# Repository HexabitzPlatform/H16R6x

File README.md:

# H16R6x-Hardware
Hexabitz 8*8 RGB LED Matrix Display Module Hardware Design

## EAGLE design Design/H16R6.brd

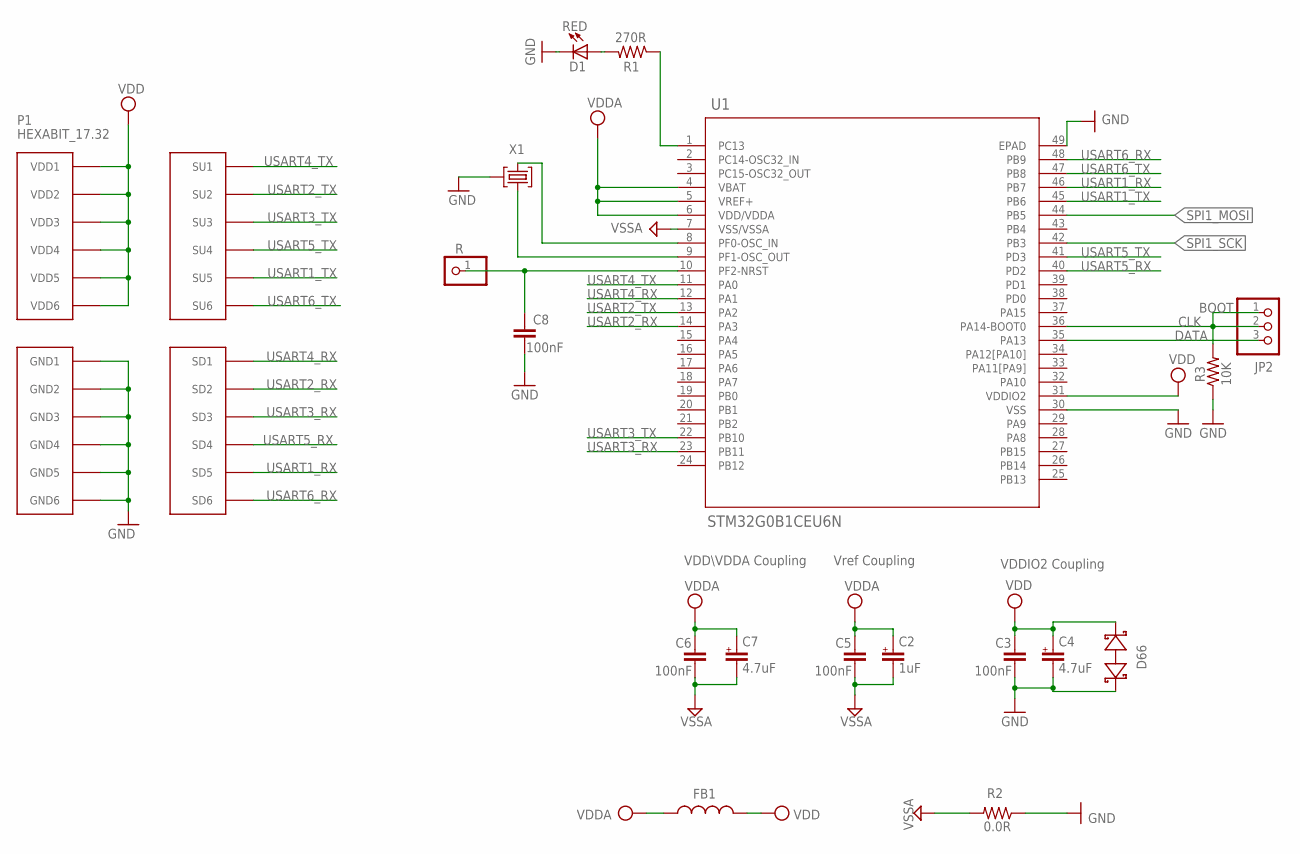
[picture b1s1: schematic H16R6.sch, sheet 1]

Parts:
C2: 1uF; C-0402-POL
C3, C5, C6, C8: 100nF; C-0402
C4, C7: 4.7uF; C-0402-POL
D1: RED; VLMS1300-GS08; MPN VLMS1300-GS08
D66: BOURNS_CDSOD323-T03SCBOURNS_CDSOD323-T03SC_0_0; BOURNS_CDSOD323-T03SC_0
FB1: FB-TDK_MMZ1608Y300B; MPN MMZ1608Y300B
JP2: PINHD-1X3; 1X03
P1: HEXABIT_17.32
R: R; 1X01
R1: 270R; R-0402
R2: 0.0R; R-0402; MPN RC0603JR-070RL
R3: 10K; R-0402
TRIMBLE-LOGO1: HEXA-LOGO
U1: STM32G0B1CEU6N; HEXABITZ_ICS_QFN_B1CEU6_STM-L
X1: XTALL_CSTCE8M00G52

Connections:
CLK: JP2.1, JP2.2, R3.2, U1.36 (PA14-BOOT0)
DATA: JP2.3, U1.35 (PA13)
GND: C3.2, C4.2, C8.2, D1.C, D66.1 (A), P1.PAD_PD7 (GND1), P1.PAD_PD8 (GND2), P1.PAD_PD9 (GND3), P1.PAD_PD10 (GND4), P1.PAD_PD11 (GND5), P1.PAD_PD12 (GND6), R2.1, R3.1, U1.30 (VSS), U1.49 (EPAD), X1.P$2 (2); also elsewhere on the board
unnamed: D1.A, R1.2
unnamed: C8.1, R.1, U1.10 (PF2-NRST)
unnamed: U1.9 (PF1-OSC_OUT), X1.P$1 (1)
unnamed: U1.8 (PF0-OSC_IN), X1.P$3 (3)
unnamed: R1.1, U1.1 (PC13)
SPI1_MOSI: U1.44 (PB5); also elsewhere on the board
SPI1_SCK: U1.42 (PB3); also elsewhere on the board
USART1_RX: P1.PAD_PD5 (SD5), U1.46 (PB7)
USART1_TX: P1.PAD_PU5 (SU5), U1.45 (PB6)
USART2_RX: P1.PAD_PD2 (SD2), U1.14 (PA3)
USART2_TX: P1.PAD_PU2 (SU2), U1.13 (PA2)
USART3_RX: P1.PAD_PD3 (SD3), U1.23 (PB11)
USART3_TX: P1.PAD_PU3 (SU3), U1.22 (PB10)
USART4_RX: P1.PAD_PD1 (SD1), U1.12 (PA1)
USART4_TX: P1.PAD_PU1 (SU1), U1.11 (PA0)
USART5_RX: P1.PAD_PD4 (SD4), U1.40 (PD2)
USART5_TX: P1.PAD_PU4 (SU4), U1.41 (PD3)
USART6_RX: P1.PAD_PD6 (SD6), U1.48 (PB9)
USART6_TX: P1.PAD_PU6 (SU6), U1.47 (PB8)
VDD: C3.1, C4.1, D66.2 (C), FB1.2, P1.PAD_PU7 (VDD1), P1.PAD_PU8 (VDD2), P1.PAD_PU9 (VDD3), P1.PAD_PU10 (VDD4), P1.PAD_PU11 (VDD5), P1.PAD_PU12 (VDD6), U1.31 (VDDIO2); also elsewhere on the board
VDDA: C2.1, C5.1, C6.1, C7.1, FB1.1, U1.4 (VBAT), U1.5 (VREF+), U1.6 (VDD/VDDA)
VSSA: C2.2, C5.2, C6.2, C7.2, R2.2, U1.7 (VSS/VSSA)

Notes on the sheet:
Vref Coupling
VDDIO2 Coupling
VDD\VDDA Coupling
BOOT

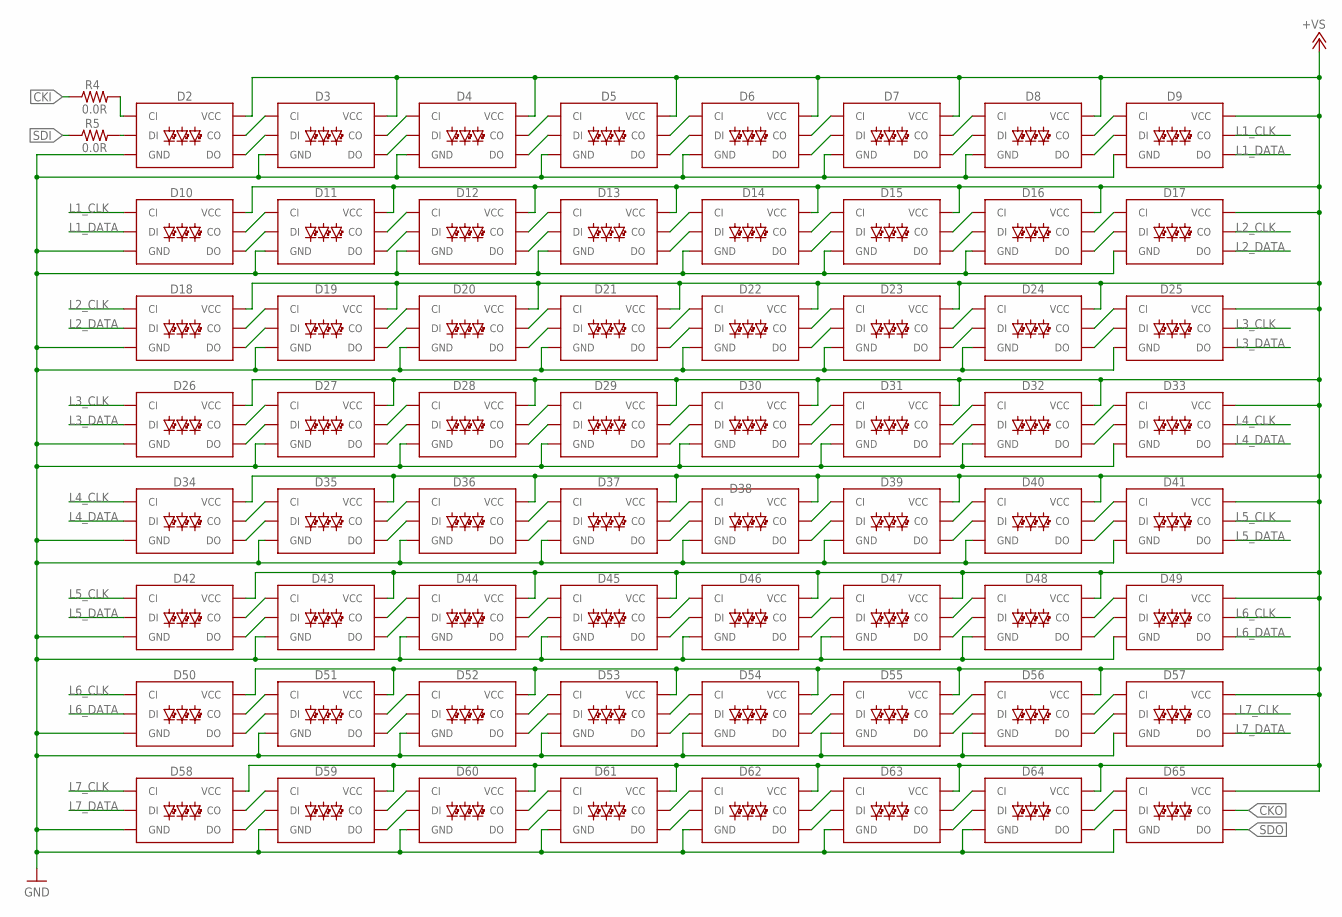
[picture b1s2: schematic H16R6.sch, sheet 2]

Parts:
D2, D3, D4, D5, D6, D7, D8, D9, D10, D11, D12, D13, D14, D15, D16, D17, D18, D19, D20, D21, D22, D23, D24, D25, D26, D27, D28, D29, D30, D31, D32, D33, D34, D35, D36, D37, D38, D39, D40, D41, D42, D43, D44, D45, D46, D47, D48, D49, D50, D51, D52, D53, D54, D55, D56, D57, D58, D59, D60, D61, D62, D63, D64, D65: SPARKFUN-LED_APA102-2020
R4, R5: 0.0R; R-0402

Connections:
+VS: D2.VDD (VCC), D2.VDD1 (VCC), D3.VDD (VCC), D3.VDD1 (VCC), D4.VDD (VCC), D4.VDD1 (VCC), D5.VDD (VCC), D5.VDD1 (VCC), D6.VDD (VCC), D6.VDD1 (VCC), D7.VDD (VCC), D7.VDD1 (VCC), D8.VDD (VCC), D8.VDD1 (VCC), D9.VDD (VCC), D9.VDD1 (VCC), D10.VDD (VCC), D10.VDD1 (VCC), D11.VDD (VCC), D11.VDD1 (VCC), D12.VDD (VCC), D12.VDD1 (VCC), D13.VDD (VCC), D13.VDD1 (VCC), D14.VDD (VCC), D14.VDD1 (VCC), D15.VDD (VCC), D15.VDD1 (VCC), D16.VDD (VCC), D16.VDD1 (VCC), D17.VDD (VCC), D17.VDD1 (VCC), D18.VDD (VCC), D18.VDD1 (VCC), D19.VDD (VCC), D19.VDD1 (VCC), D20.VDD (VCC), D20.VDD1 (VCC), D21.VDD (VCC), D21.VDD1 (VCC), D22.VDD (VCC), D22.VDD1 (VCC), D23.VDD (VCC), D23.VDD1 (VCC), D24.VDD (VCC), D24.VDD1 (VCC), D25.VDD (VCC), D25.VDD1 (VCC), D26.VDD (VCC), D26.VDD1 (VCC), D27.VDD (VCC), D27.VDD1 (VCC), D28.VDD (VCC), D28.VDD1 (VCC), D29.VDD (VCC), D29.VDD1 (VCC), D30.VDD (VCC), D30.VDD1 (VCC), D31.VDD (VCC), D31.VDD1 (VCC), D32.VDD (VCC), D32.VDD1 (VCC), D33.VDD (VCC), D33.VDD1 (VCC), D34.VDD (VCC), D34.VDD1 (VCC), D35.VDD (VCC), D35.VDD1 (VCC), D36.VDD (VCC), D36.VDD1 (VCC), D37.VDD (VCC), D37.VDD1 (VCC), D38.VDD (VCC), D38.VDD1 (VCC), D39.VDD (VCC), D39.VDD1 (VCC), D40.VDD (VCC), D40.VDD1 (VCC), D41.VDD (VCC), D41.VDD1 (VCC), D42.VDD (VCC), D42.VDD1 (VCC), D43.VDD (VCC), D43.VDD1 (VCC), D44.VDD (VCC), D44.VDD1 (VCC), D45.VDD (VCC), D45.VDD1 (VCC), D46.VDD (VCC), D46.VDD1 (VCC), D47.VDD (VCC), D47.VDD1 (VCC), D48.VDD (VCC), D48.VDD1 (VCC), D49.VDD (VCC), D49.VDD1 (VCC), D50.VDD (VCC), D50.VDD1 (VCC), D51.VDD (VCC), D51.VDD1 (VCC), D52.VDD (VCC), D52.VDD1 (VCC), D53.VDD (VCC), D53.VDD1 (VCC), D54.VDD (VCC), D54.VDD1 (VCC), D55.VDD (VCC), D55.VDD1 (VCC), D56.VDD (VCC), D56.VDD1 (VCC), D57.VDD (VCC), D57.VDD1 (VCC), D58.VDD (VCC), D58.VDD1 (VCC), D59.VDD (VCC), D59.VDD1 (VCC), D60.VDD (VCC), D60.VDD1 (VCC), D61.VDD (VCC), D61.VDD1 (VCC), D62.VDD (VCC), D62.VDD1 (VCC), D63.VDD (VCC), D63.VDD1 (VCC), D64.VDD (VCC), D64.VDD1 (VCC), D65.VDD (VCC), D65.VDD1 (VCC); also elsewhere on the board
CKI: R4.1; also elsewhere on the board
CKO: D65.CO; also elsewhere on the board
GND: D2.GND, D3.GND, D4.GND, D5.GND, D6.GND, D7.GND, D8.GND, D9.GND, D10.GND, D11.GND, D12.GND, D13.GND, D14.GND, D15.GND, D16.GND, D17.GND, D18.GND, D19.GND, D20.GND, D21.GND, D22.GND, D23.GND, D24.GND, D25.GND, D26.GND, D27.GND, D28.GND, D29.GND, D30.GND, D31.GND, D32.GND, D33.GND, D34.GND, D35.GND, D36.GND, D37.GND, D38.GND, D39.GND, D40.GND, D41.GND, D42.GND, D43.GND, D44.GND, D45.GND, D46.GND, D47.GND, D48.GND, D49.GND, D50.GND, D51.GND, D52.GND, D53.GND, D54.GND, D55.GND, D56.GND, D57.GND, D58.GND, D59.GND, D60.GND, D61.GND, D62.GND, D63.GND, D64.GND, D65.GND; also elsewhere on the board
L1_CLK: D9.CO, D10.CI
L1_DATA: D9.DO, D10.DI
L2_CLK: D17.CO, D18.CI
L2_DATA: D17.DO, D18.DI
L3_CLK: D25.CO, D26.CI
L3_DATA: D25.DO, D26.DI
L4_CLK: D33.CO, D34.CI
L4_DATA: D33.DO, D34.DI
L5_CLK: D41.CO, D42.CI
L5_DATA: D41.DO, D42.DI
L6_CLK: D49.CO, D50.CI
L6_DATA: D49.DO, D50.DI
L7_CLK: D57.CO, D58.CI
L7_DATA: D57.DO, D58.DI
unnamed: D3.DO, D4.DI
unnamed: D3.CO, D4.CI
unnamed: D2.DO, D3.DI
unnamed: D2.CO, D3.CI
unnamed: D8.DO, D9.DI
unnamed: D8.CO, D9.CI
unnamed: D7.CO, D8.CI
unnamed: D7.DO, D8.DI
unnamed: D5.CO, D6.CI
unnamed: D5.DO, D6.DI
unnamed: D16.CO, D17.CI
unnamed: D16.DO, D17.DI
unnamed: D10.CO, D11.CI
unnamed: D10.DO, D11.DI
unnamed: D11.CO, D12.CI
unnamed: D11.DO, D12.DI
unnamed: D12.CO, D13.CI
unnamed: D18.CO, D19.CI
unnamed: D18.DO, D19.DI
unnamed: D19.CO, D20.CI
unnamed: D19.DO, D20.DI
unnamed: D20.CO, D21.CI
unnamed: D20.DO, D21.DI
unnamed: D21.CO, D22.CI
unnamed: D21.DO, D22.DI
unnamed: D22.CO, D23.CI
unnamed: D22.DO, D23.DI
unnamed: D23.CO, D24.CI
unnamed: D23.DO, D24.DI
unnamed: D24.CO, D25.CI
unnamed: D24.DO, D25.DI
unnamed: D26.CO, D27.CI
unnamed: D26.DO, D27.DI
unnamed: D27.CO, D28.CI
unnamed: D27.DO, D28.DI
unnamed: D28.CO, D29.CI
unnamed: D28.DO, D29.DI
unnamed: D29.CO, D30.CI
unnamed: D29.DO, D30.DI
unnamed: D31.CO, D32.CI
unnamed: D31.DO, D32.DI
unnamed: D30.CO, D31.CI
unnamed: D30.DO, D31.DI
unnamed: D32.CO, D33.CI
unnamed: D32.DO, D33.DI
unnamed: D34.CO, D35.CI
unnamed: D34.DO, D35.DI
unnamed: D35.CO, D36.CI
unnamed: D35.DO, D36.DI
unnamed: D36.CO, D37.CI
unnamed: D36.DO, D37.DI
unnamed: D37.CO, D38.CI
unnamed: D37.DO, D38.DI
unnamed: D38.CO, D39.CI
unnamed: D38.DO, D39.DI
unnamed: D40.CO, D41.CI
unnamed: D40.DO, D41.DI
unnamed: D39.CO, D40.CI
unnamed: D39.DO, D40.DI
unnamed: D48.CO, D49.CI
unnamed: D48.DO, D49.DI
unnamed: D56.CO, D57.CI
unnamed: D56.DO, D57.DI
unnamed: D64.CO, D65.CI
unnamed: D64.DO, D65.DI
unnamed: D55.DO, D56.DI
unnamed: D55.CO, D56.CI
unnamed: D63.CO, D64.CI
unnamed: D63.DO, D64.DI
unnamed: D54.CO, D55.CI
unnamed: D54.DO, D55.DI
unnamed: D62.CO, D63.CI
unnamed: D62.DO, D63.DI
unnamed: D61.DO, D62.DI
unnamed: D61.CO, D62.CI
unnamed: D60.CO, D61.CI
unnamed: D60.DO, D61.DI
unnamed: D59.CO, D60.CI
unnamed: D59.DO, D60.DI
unnamed: D58.DO, D59.DI
unnamed: D58.CO, D59.CI
unnamed: D53.DO, D54.DI
unnamed: D53.CO, D54.CI
unnamed: D51.CO, D52.CI
unnamed: D51.DO, D52.DI
unnamed: D52.DO, D53.DI
unnamed: D52.CO, D53.CI
unnamed: D50.DO, D51.DI
unnamed: D50.CO, D51.CI
unnamed: D42.CO, D43.CI
unnamed: D42.DO, D43.DI
unnamed: D43.CO, D44.CI
unnamed: D43.DO, D44.DI
unnamed: D44.CO, D45.CI
unnamed: D44.DO, D45.DI
unnamed: D45.DO, D46.DI
unnamed: D45.CO, D46.CI
unnamed: D46.CO, D47.CI
unnamed: D46.DO, D47.DI
unnamed: D47.CO, D48.CI
unnamed: D47.DO, D48.DI
unnamed: D12.DO, D13.DI
unnamed: D13.DO, D14.DI
unnamed: D13.CO, D14.CI
unnamed: D14.CO, D15.CI
unnamed: D14.DO, D15.DI
unnamed: D15.CO, D16.CI
unnamed: D15.DO, D16.DI
unnamed: D4.CO, D5.CI
unnamed: D4.DO, D5.DI
unnamed: D6.CO, D7.CI
unnamed: D6.DO, D7.DI
unnamed: D2.DI, R5.2
unnamed: D2.CI, R4.2
SDI: R5.1; also elsewhere on the board
SDO: D65.DO; also elsewhere on the board

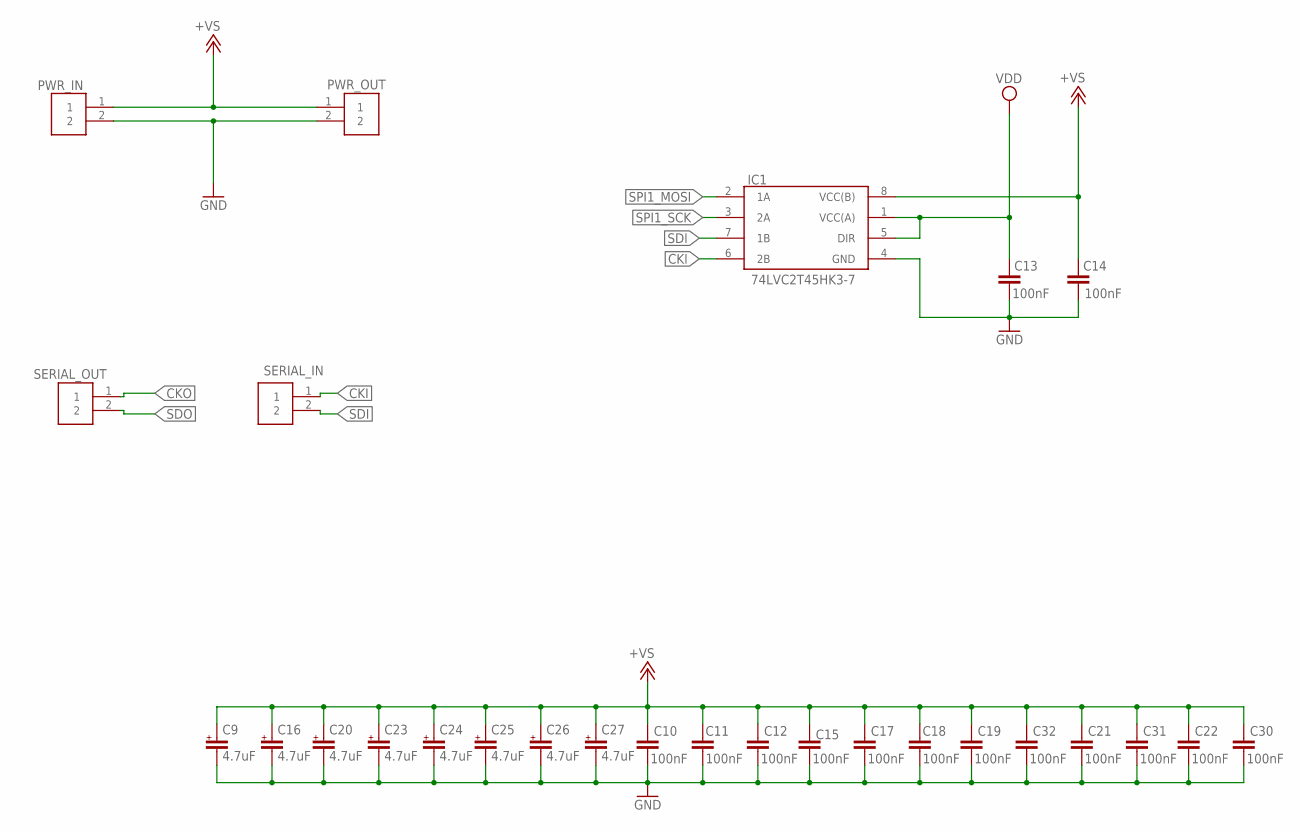
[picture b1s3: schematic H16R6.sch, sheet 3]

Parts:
C9, C16, C20, C23, C24, C25, C26, C27: 4.7uF; C-0402-POL
C10, C11, C12, C13, C14, C15, C17, C18, C19, C21, C22, C30, C31, C32: 100nF; C-0402
IC1: 74LVC2T45HK3-7; 74LVC2T45HK37
PWR_IN: 3-644456-2; TE_3-644456-2
PWR_OUT: 3-644456-2; TE_3-644456-2
SERIAL_IN: 3-644456-2; TE_3-644456-2
SERIAL_OUT: 3-644456-2; TE_3-644456-2

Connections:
+VS: C9.1, C10.1, C11.1, C12.1, C14.1, C15.1, C16.1, C17.1, C18.1, C19.1, C20.1, C21.1, C22.1, C23.1, C24.1, C25.1, C26.1, C27.1, C30.1, C31.1, C32.1, IC1.8 (VCC(B)), PWR_IN.1, PWR_OUT.1; also elsewhere on the board
CKI: IC1.6 (2B), SERIAL_IN.1; also elsewhere on the board
CKO: SERIAL_OUT.1; also elsewhere on the board
GND: C9.2, C10.2, C11.2, C12.2, C13.2, C14.2, C15.2, C16.2, C17.2, C18.2, C19.2, C20.2, C21.2, C22.2, C23.2, C24.2, C25.2, C26.2, C27.2, C30.2, C31.2, C32.2, IC1.4 (GND), PWR_IN.2, PWR_OUT.2; also elsewhere on the board
SDI: IC1.7 (1B), SERIAL_IN.2; also elsewhere on the board
SDO: SERIAL_OUT.2; also elsewhere on the board
SPI1_MOSI: IC1.2 (1A); also elsewhere on the board
SPI1_SCK: IC1.3 (2A); also elsewhere on the board
VDD: C13.1, IC1.1 (VCC(A)), IC1.5 (DIR); also elsewhere on the board

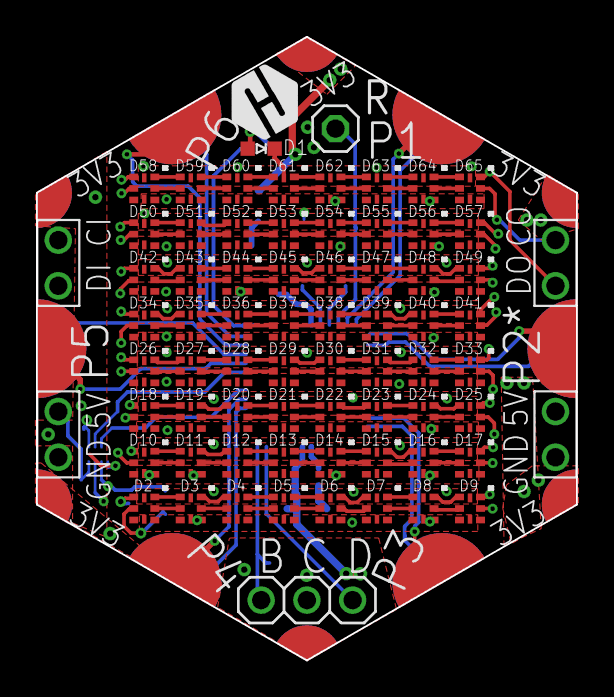
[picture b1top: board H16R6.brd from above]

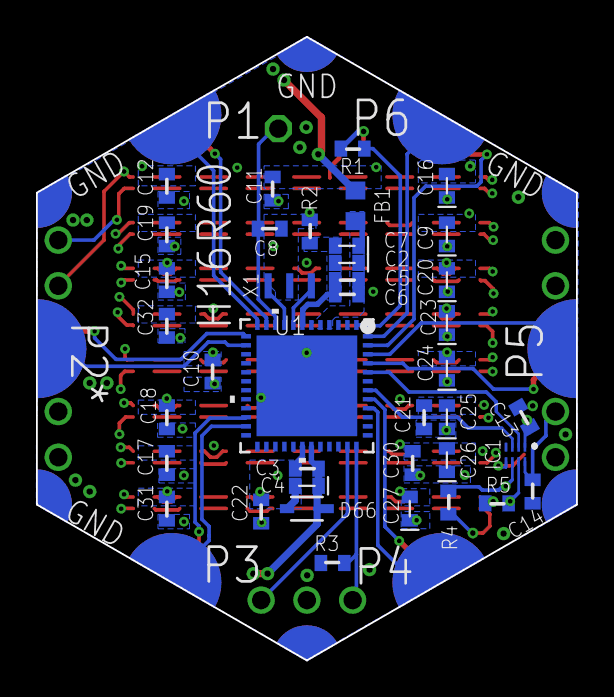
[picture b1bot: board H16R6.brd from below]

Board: 4 copper layers, 30.0 x 34.6 mm, 112 parts (39 on the bottom side), 158 nets.

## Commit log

2024-02-10 Reviewed Version, all finished.
2024-02-24 -Fix the LEDs quantity in the BOM
2024-04-12 Edit the logo Add the TVS diode
2024-04-17 no message
2024-04-17 Replace the led APA-102-2020-6 with APA-102-2020-8
2024-04-26 Fix the clearance and soldermask issues Replace the 0603 4.7uF tant cap with ceramic cap in the BOM
2024-04-29 Fix BOM

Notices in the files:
parts and their libraries:
HEXABITZ_ICs: COPYRIGHT: Copyright (C) 2022 Ultra Librarian. All rights reserved.
